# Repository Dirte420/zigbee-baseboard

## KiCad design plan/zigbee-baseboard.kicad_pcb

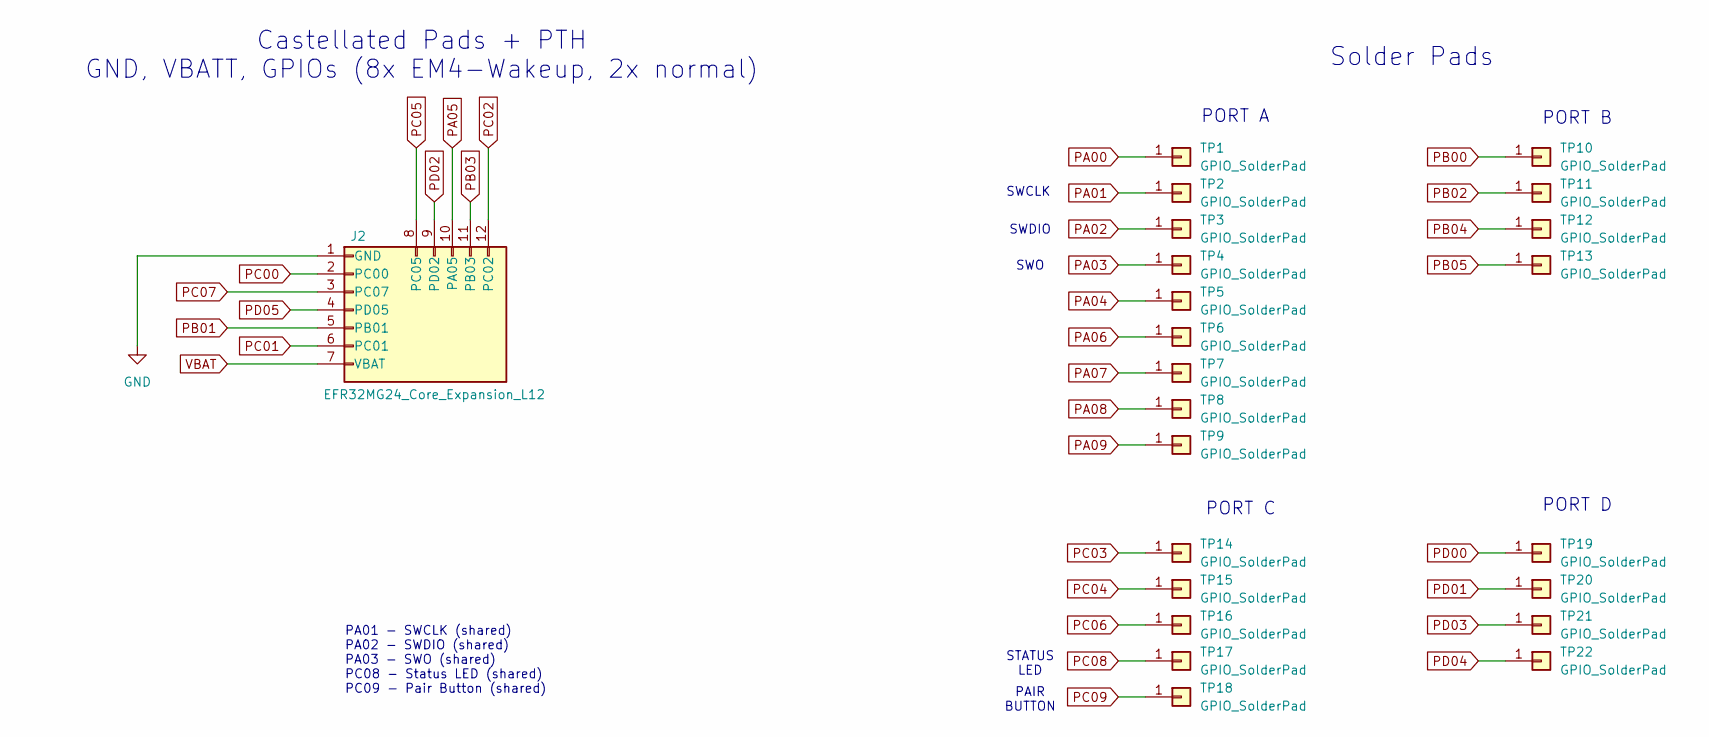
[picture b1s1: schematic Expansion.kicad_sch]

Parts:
J2: EFR32MG24_Core_Expansion_L12; Module_EFR32MG24_Core_Castellated_L_12Pin_P2.54mm
TP1, TP2, TP3, TP4, TP5, TP6, TP7, TP8, TP9, TP10, TP11, TP12, TP13, TP14, TP15, TP16, TP17, TP18, TP19, TP20, TP21, TP22: GPIO_SolderPad; GPIO_SolderPad_D1.0mm_Bottom

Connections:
GND: J2.1 (GND); also elsewhere on the board
PA00: TP1.1; also elsewhere on the board
PA01: TP2.1; also elsewhere on the board
PA02: TP3.1; also elsewhere on the board
PA03: TP4.1; also elsewhere on the board
PA04: TP5.1; also elsewhere on the board
PA05: J2.10 (PA05); also elsewhere on the board
PA06: TP6.1; also elsewhere on the board
PA07: TP7.1; also elsewhere on the board
PA08: TP8.1; also elsewhere on the board
PA09: TP9.1; also elsewhere on the board
PB00: TP10.1; also elsewhere on the board
PB01: J2.5 (PB01); also elsewhere on the board
PB02: TP11.1; also elsewhere on the board
PB03: J2.11 (PB03); also elsewhere on the board
PB04: TP12.1; also elsewhere on the board
PB05: TP13.1; also elsewhere on the board
PC00: J2.2 (PC00); also elsewhere on the board
PC01: J2.6 (PC01); also elsewhere on the board
PC02: J2.12 (PC02); also elsewhere on the board
PC03: TP14.1; also elsewhere on the board
PC04: TP15.1; also elsewhere on the board
PC05: J2.8 (PC05); also elsewhere on the board
PC06: TP16.1; also elsewhere on the board
PC07: J2.3 (PC07); also elsewhere on the board
PC08: TP17.1; also elsewhere on the board
PC09: TP18.1; also elsewhere on the board
PD00: TP19.1; also elsewhere on the board
PD01: TP20.1; also elsewhere on the board
PD02: J2.9 (PD02); also elsewhere on the board
PD03: TP21.1; also elsewhere on the board
PD04: TP22.1; also elsewhere on the board
PD05: J2.4 (PD05); also elsewhere on the board
VBAT: J2.7 (VBAT); also elsewhere on the board

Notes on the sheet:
PA01 - SWCLK (shared) PA02 - SWDIO (shared) PA03 - SWO (shared) PC08 - Status LED (shared) PC09 - Pair Button (shared)
PORT C
Castellated Pads + PTH GND, VBATT, GPIOs (8x EM4-Wakeup, 2x normal)
SWCLK
SWDIO
PORT B
PAIR BUTTON
PORT D
STATUS LED
Solder Pads
SWO
PORT A

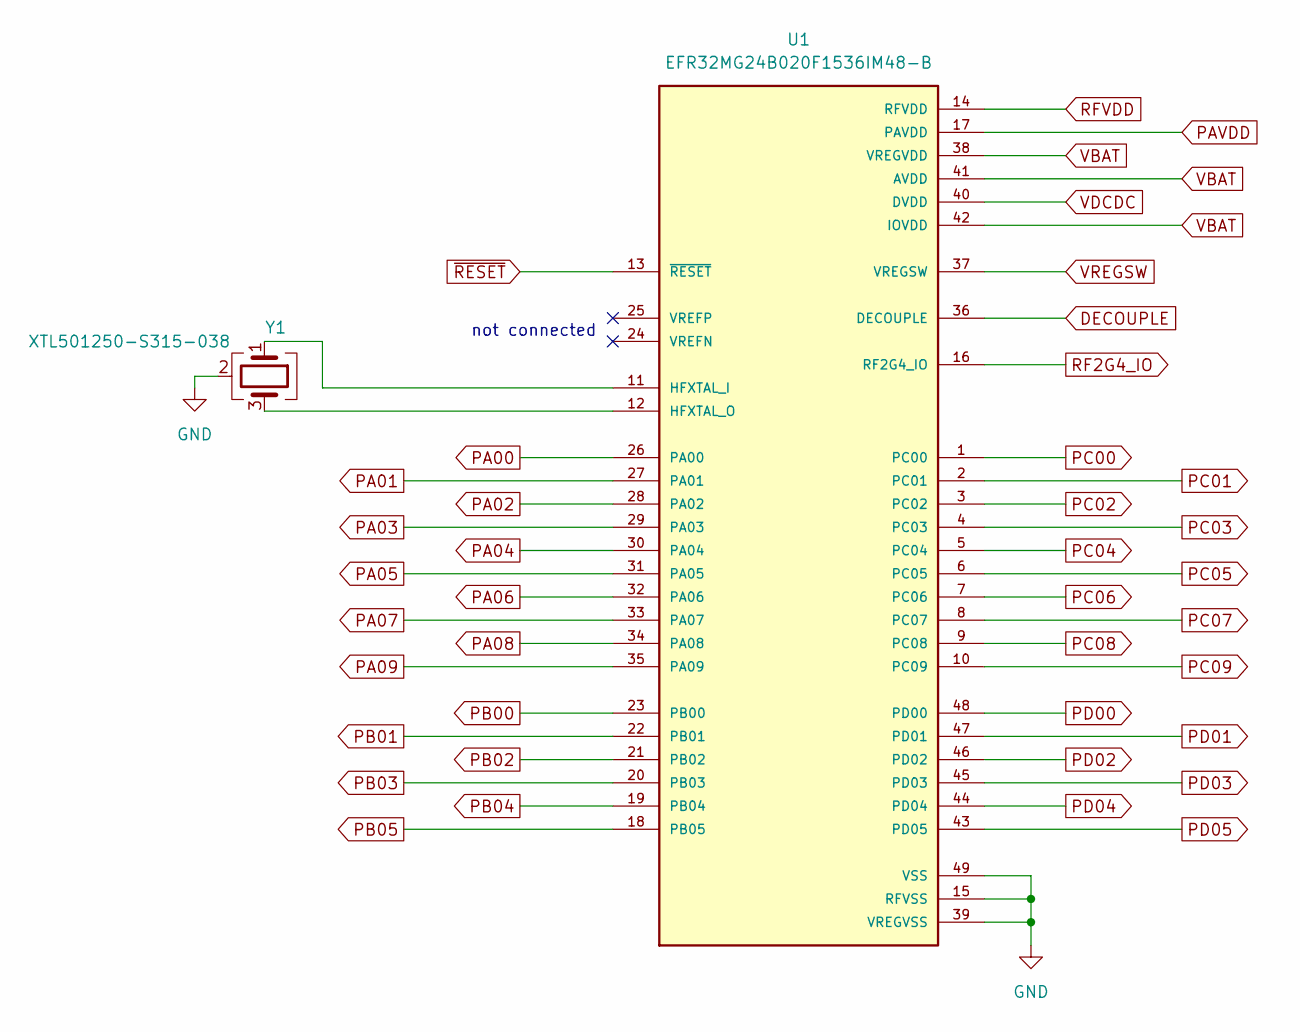
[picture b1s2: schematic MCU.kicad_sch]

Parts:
U1: EFR32MG24B020F1536IM48-B; QFN-48-1EP_6x6mm_P0.4mm_EFR32MG24
Y1: XTL501250-S315-038; Crystal_Siward_XTL501250_2.0x1.6mm

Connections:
DECOUPLE: U1.36 (DECOUPLE); also elsewhere on the board
GND: U1.15 (RFVSS), U1.39 (VREGVSS), U1.49 (VSS), Y1.2 (G), Y1.4 (G); also elsewhere on the board
unnamed: U1.11 (HFXTAL_I), Y1.1
unnamed: U1.12 (HFXTAL_O), Y1.3
PA00: U1.26 (PA00); also elsewhere on the board
PA01: U1.27 (PA01); also elsewhere on the board
PA02: U1.28 (PA02); also elsewhere on the board
PA03: U1.29 (PA03); also elsewhere on the board
PA04: U1.30 (PA04); also elsewhere on the board
PA05: U1.31 (PA05); also elsewhere on the board
PA06: U1.32 (PA06); also elsewhere on the board
PA07: U1.33 (PA07); also elsewhere on the board
PA08: U1.34 (PA08); also elsewhere on the board
PA09: U1.35 (PA09); also elsewhere on the board
PAVDD: U1.17 (PAVDD); also elsewhere on the board
PB00: U1.23 (PB00); also elsewhere on the board
PB01: U1.22 (PB01); also elsewhere on the board
PB02: U1.21 (PB02); also elsewhere on the board
PB03: U1.20 (PB03); also elsewhere on the board
PB04: U1.19 (PB04); also elsewhere on the board
PB05: U1.18 (PB05); also elsewhere on the board
PC00: U1.1 (PC00); also elsewhere on the board
PC01: U1.2 (PC01); also elsewhere on the board
PC02: U1.3 (PC02); also elsewhere on the board
PC03: U1.4 (PC03); also elsewhere on the board
PC04: U1.5 (PC04); also elsewhere on the board
PC05: U1.6 (PC05); also elsewhere on the board
PC06: U1.7 (PC06); also elsewhere on the board
PC07: U1.8 (PC07); also elsewhere on the board
PC08: U1.9 (PC08); also elsewhere on the board
PC09: U1.10 (PC09); also elsewhere on the board
PD00: U1.48 (PD00); also elsewhere on the board
PD01: U1.47 (PD01); also elsewhere on the board
PD02: U1.46 (PD02); also elsewhere on the board
PD03: U1.45 (PD03); also elsewhere on the board
PD04: U1.44 (PD04); also elsewhere on the board
PD05: U1.43 (PD05); also elsewhere on the board
RF2G4_IO: U1.16 (RF2G4_IO); also elsewhere on the board
RFVDD: U1.14 (RFVDD); also elsewhere on the board
VBAT: U1.38 (VREGVDD), U1.41 (AVDD), U1.42 (IOVDD); also elsewhere on the board
VDCDC: U1.40 (DVDD); also elsewhere on the board
VREGSW: U1.37 (VREGSW); also elsewhere on the board
~RESET: U1.13 (~RESET); also elsewhere on the board

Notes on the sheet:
not connected

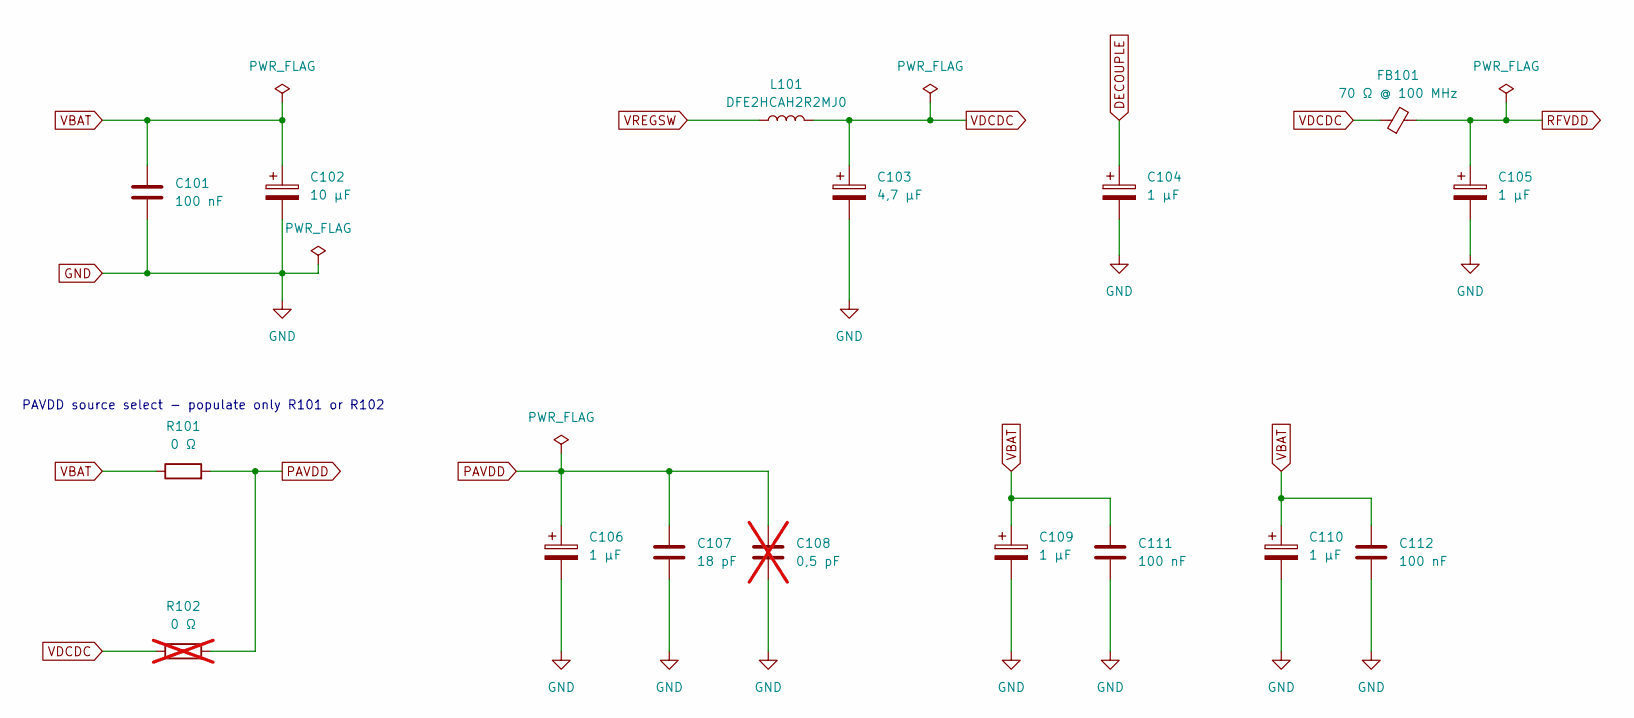
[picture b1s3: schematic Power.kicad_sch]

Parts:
C101, C111, C112: 100 nF; C_0402_1005Metric
C102: 10 µF; C_0603_1608Metric
C103: 4,7 µF; C_0603_1608Metric
C104, C105, C106, C109, C110: 1 µF; C_0402_1005Metric
C107: 18 pF; C_0201_0603Metric
C108: 0,5 pF; C_0201_0603Metric; not fitted
FB101: 70 Ω @ 100 MHz; L_0201_0603Metric
L101: DFE2HCAH2R2MJ0; Inductor_Murata_DFE2HCAH_2520; MPN DFE2HCAH2R2MJ0
R101: 0 Ω; R_0402_1005Metric
R102: 0 Ω; R_0402_1005Metric; not fitted

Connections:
DECOUPLE: C104.1; also elsewhere on the board
GND: C101.2, C102.2, C103.2, C104.2, C105.2, C106.2, C107.2, C108.2, C109.2, C110.2, C111.2, C112.2; also elsewhere on the board
PAVDD: C106.1, C107.1, C108.1, R101.2, R102.2; also elsewhere on the board
RFVDD: C105.1, FB101.2; also elsewhere on the board
VBAT: C101.1, C102.1, C109.1, C110.1, C111.1, C112.1, R101.1; also elsewhere on the board
VDCDC: C103.1, FB101.1, L101.2, R102.1; also elsewhere on the board
VREGSW: L101.1; also elsewhere on the board

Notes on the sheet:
PAVDD source select - populate only R101 or R102

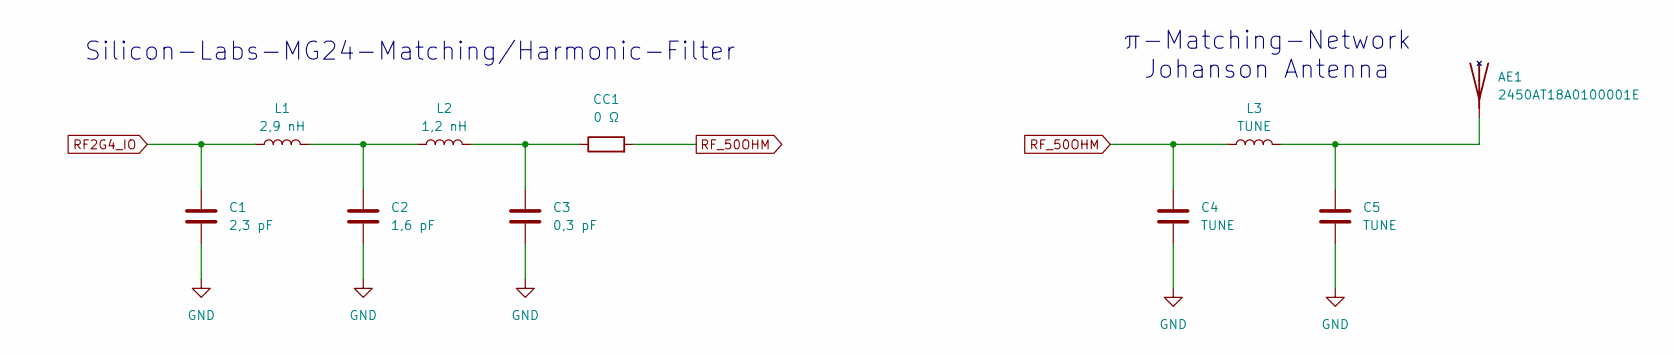
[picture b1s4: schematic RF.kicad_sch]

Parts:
AE1: 2450AT18A0100001E; Antenna_Johanson_2450AT18A0100001E
C1: 2,3 pF; C_0201_0603Metric
C2: 1,6 pF; C_0201_0603Metric
C3: 0,3 pF; C_0201_0603Metric
C4, C5: TUNE; C_0201_0603Metric
CC1: 0 Ω; R_0201_0603Metric
L1: 2,9 nH; L_0201_0603Metric
L2: 1,2 nH; L_0201_0603Metric
L3: TUNE; L_0201_0603Metric

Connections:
GND: C1.2, C2.2, C3.2, C4.2, C5.2; also elsewhere on the board
unnamed: AE1.1 (FEED_1), C5.1, L3.2
unnamed: C2.1, L1.2, L2.1
unnamed: C3.1, CC1.1, L2.2
RF2G4_IO: C1.1, L1.1; also elsewhere on the board
RF_50OHM: C4.1, CC1.2, L3.1

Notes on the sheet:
π-Matching-Network Johanson Antenna
Silicon-Labs-MG24-Matching/Harmonic-Filter

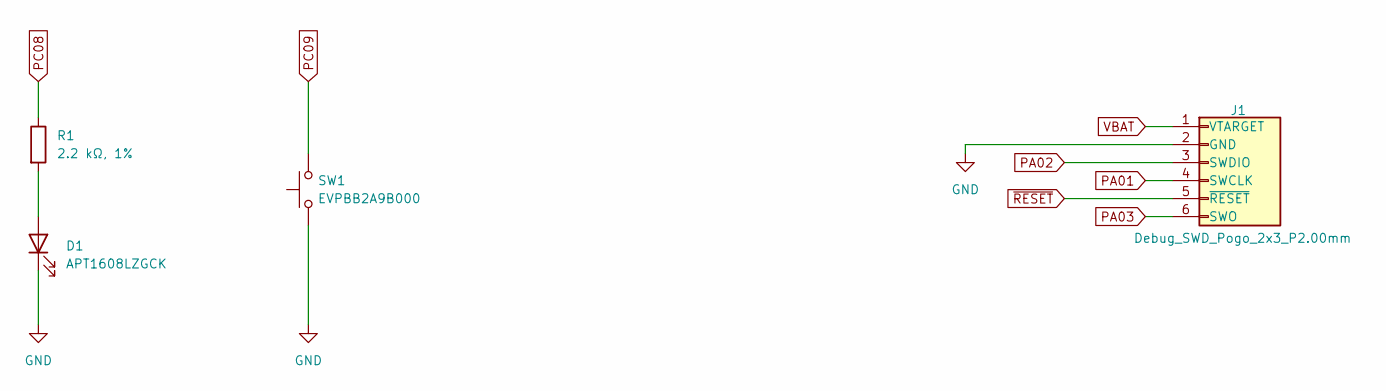
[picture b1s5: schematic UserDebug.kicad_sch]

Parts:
D1: APT1608LZGCK; LED_0603_1608Metric
J1: Debug_SWD_Pogo_2x3_P2.00mm
R1: 2.2 kΩ, 1%; R_0402_1005Metric
SW1: EVPBB2A9B000; Button_Panasonic_EVPBB_2.6x1.6mm

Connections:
GND: D1.1 (K), J1.2 (GND), SW1.1; also elsewhere on the board
unnamed: D1.2 (A), R1.2
PA01: J1.4 (SWCLK); also elsewhere on the board
PA02: J1.3 (SWDIO); also elsewhere on the board
PA03: J1.6 (SWO); also elsewhere on the board
PC08: R1.1; also elsewhere on the board
PC09: SW1.2; also elsewhere on the board
VBAT: J1.1 (VTARGET); also elsewhere on the board
~RESET: J1.5 (~RESET); also elsewhere on the board

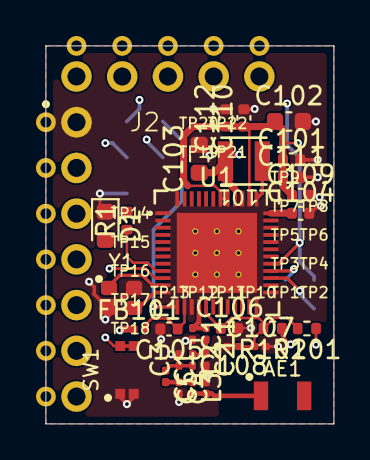
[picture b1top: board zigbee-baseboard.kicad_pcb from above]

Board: 4 copper layers, 16.0 x 21.0 mm, 55 parts (0 on the bottom side), 48 nets.
